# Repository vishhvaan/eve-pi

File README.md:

The EVE is an open framework for an automated continuous culture system.

  - Easy to use for programmers and non-programmers
  - Cheap
  - Replicate functionality of a morbidostat/chemostat/turbidostat
  - Versatile & easily modifiable for different purposes

This device is meant to be used for the study of population dynamics and evolution.

# Build it!
Head over to [Start Building] folder to find the 3D stls and circuit schematics (along with KiCAD project). 

# Installation

1. Download and flash the [Raspbian] Buster OS on an SD card.
2. Insert the SD Card into the Pi and connect the Pi to a display, keyboard, local area network, and power.
3. Note the IP address of the device with the command:
```sh
$ ifconfig
```
4. Enter super user mode with the command:
```sh
$ sudo su
```  
5. Run the setup script by entering the command: 
```sh
$ bash <(curl -s https://raw.githubusercontent.com/vishhvaan/eve-pi/master/st_eve.sh)
```
6. Follow the on-screen instructions to install the software.
7. Navigate to the folder `scripts/live/` and copy the `sample-conf.in` to `eve-conf.ini`.
8. Edit the `eve-conf.ini` file based on the "Configuration File Parameter Definitions" file in the "Start Building" folder.\*
9. If the Pi has a browser, navigate to the web interface by accessing: http://localhost.
10. On a browser on the network, navigate to the web interface by accessing the IP address or hostname of the device (e.g. http://eve.local_domain.net).

\* If the PCB is used or the breadboard was wired like the schematic, the default values for the hardware address in the sample-conf.ini file will work.

For a headless install:

1. Download and flash the [Raspbian] Buster OS on an SD card.
2. Add a file titled `ssh` to the boot partition.
3. Insert the SD Card into the Pi and connect the Pi to the local area network and power.
4. In a seperate computer's terminal run a command to connect to the pi.
```sh
$ ssh pi@raspberrypi
```  
5. Login to the pi with the password `raspberry`
6. Continue from step 3 in the non-headless install.

## Install for Docker for ARM Devices
 
Pre-built images coming soon to Docker Hub!

### Build the Docker Image

Use the Dockerfiles in the repo to build images yourself. Use the images to spin up containers in the Pi with EVE WebUI and all the programs built-in.

#### On ARM Devices

1. [Install Docker] on the Raspberry Pi.
2. Install git on the Raspberry Pi.
```sh
$ sudo apt install -y git
```  
2. Clone the repository to the home directory.
```sh
$ sudo git clone https://github.com/vishhvaan/eve-pi.git /eve
```  
3. Move to the correct directory.
```sh
$ cd /eve
``` 
4. Run the Docker build command.
```sh
$ docker build -t eve:pi .
```  
5. Create a container.
```sh
$ docker create --name = eve1 \
    -p 80:80 \
    -p 8050:8050 \
    -e PUID=1000 \
    -e PGID=1000 \
    -v /eve/data:/data \
    eve:pi
```  
6. Start the container.
```sh
$ docker start eve1
```  

#### On UNIX-based x86/x64 Devices
Emulate the ARM environment with QEMU. Build images with the Dockerfile.arm32v7.

### Shout Outs
The EVE uses a number of open source projects to work properly:

  - [script-server] -  Script server to run programs on the Pi
  - [slack-api] - Uses the Slack API for Python for experiment monitoring
  - [plotly] - Uses Dash for real-time plotting
  - [KiCAD] - For Circuit Schematics and PCB Designs
  - [Docker] - For creating self-contained application platforms

## New Features
 
  - Configurable save locations (USB or Network)
  - Combined graphs of culture units

<!---->

License
----

MIT

   [script-server]: <https://github.com/bugy/script-server>
   [slack-api]: <https://github.com/slackapi/python-slackclient>
   [Start Building]: <https://github.com/vishhvaan/eve-pi/tree/master/Start%20Building>
   [plotly]: <https://plot.ly/dash/>
   [KiCad]: <http://www.kicad.org/>
   [Install Docker]: <https://github.com/docker/docker-install>
   [Raspbian]: <https://www.raspberrypi.org/downloads/raspbian/>
   [Docker]: <https://github.com/docker/docker-ce>

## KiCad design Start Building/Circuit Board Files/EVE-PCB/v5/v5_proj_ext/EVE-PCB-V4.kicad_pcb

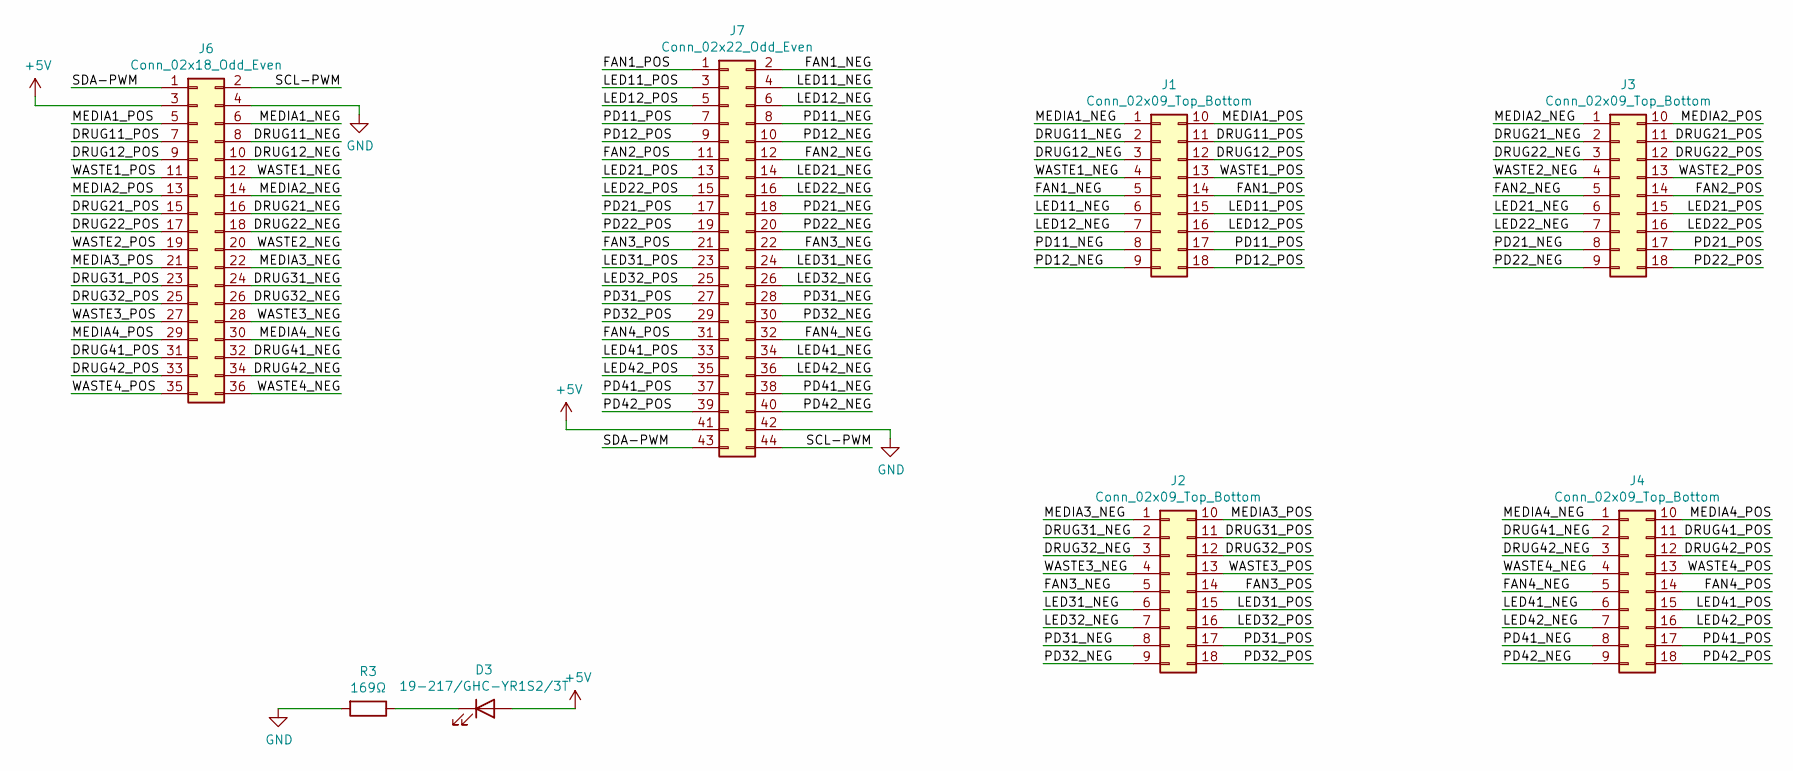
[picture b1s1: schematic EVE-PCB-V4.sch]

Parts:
D3: 19-217/GHC-YR1S2/3T; LED_0603_1608Metric; LCSC C72043
J1, J2, J3, J4: Conn_02x09_Top_Bottom; 282888-7
J6: Conn_02x18_Odd_Even; PinHeader_2x18_P2.54mm_Vertical
J7: Conn_02x22_Odd_Even; PinHeader_2x22_P2.54mm_Vertical
R3: 169Ω; R_0805_2012Metric; LCSC C17489

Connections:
+5V: D3.2 (A), J6.3, J7.41
/DRUG11_NEG: J1.2, J6.8
/DRUG11_POS: J1.11, J6.7
/DRUG12_NEG: J1.3, J6.10
/DRUG12_POS: J1.12, J6.9
/DRUG21_NEG: J3.2, J6.16
/DRUG21_POS: J3.11, J6.15
/DRUG22_NEG: J3.3, J6.18
/DRUG22_POS: J3.12, J6.17
/DRUG31_NEG: J2.2, J6.24
/DRUG31_POS: J2.11, J6.23
/DRUG32_NEG: J2.3, J6.26
/DRUG32_POS: J2.12, J6.25
/DRUG41_NEG: J4.2, J6.32
/DRUG41_POS: J4.11, J6.31
/DRUG42_NEG: J4.3, J6.34
/DRUG42_POS: J4.12, J6.33
/FAN1_NEG: J1.5, J7.2
/FAN1_POS: J1.14, J7.1
/FAN2_NEG: J3.5, J7.12
/FAN2_POS: J3.14, J7.11
/FAN3_NEG: J2.5, J7.22
/FAN3_POS: J2.14, J7.21
/FAN4_NEG: J4.5, J7.32
/FAN4_POS: J4.14, J7.31
/LED11_NEG: J1.6, J7.4
/LED11_POS: J1.15, J7.3
/LED12_NEG: J1.7, J7.6
/LED12_POS: J1.16, J7.5
/LED21_NEG: J3.6, J7.14
/LED21_POS: J3.15, J7.13
/LED22_NEG: J3.7, J7.16
/LED22_POS: J3.16, J7.15
/LED31_NEG: J2.6, J7.24
/LED31_POS: J2.15, J7.23
/LED32_NEG: J2.7, J7.26
/LED32_POS: J2.16, J7.25
/LED41_NEG: J4.6, J7.34
/LED41_POS: J4.15, J7.33
/LED42_NEG: J4.7, J7.36
/LED42_POS: J4.16, J7.35
/MEDIA1_NEG: J1.1, J6.6
/MEDIA1_POS: J1.10, J6.5
/MEDIA2_NEG: J3.1, J6.14
/MEDIA2_POS: J3.10, J6.13
/MEDIA3_NEG: J2.1, J6.22
/MEDIA3_POS: J2.10, J6.21
/MEDIA4_NEG: J4.1, J6.30
/MEDIA4_POS: J4.10, J6.29
/PD11_NEG: J1.8, J7.8
/PD11_POS: J1.17, J7.7
/PD12_NEG: J1.9, J7.10
/PD12_POS: J1.18, J7.9
/PD21_NEG: J3.8, J7.18
/PD21_POS: J3.17, J7.17
/PD22_NEG: J3.9, J7.20
/PD22_POS: J3.18, J7.19
/PD31_NEG: J2.8, J7.28
/PD31_POS: J2.17, J7.27
/PD32_NEG: J2.9, J7.30
/PD32_POS: J2.18, J7.29
/PD41_NEG: J4.8, J7.38
/PD41_POS: J4.17, J7.37
/PD42_NEG: J4.9, J7.40
/PD42_POS: J4.18, J7.39
/SCL-PWM: J6.2, J7.44
/SDA-PWM: J6.1, J7.43
/WASTE1_NEG: J1.4, J6.12
/WASTE1_POS: J1.13, J6.11
/WASTE2_NEG: J3.4, J6.20
/WASTE2_POS: J3.13, J6.19
/WASTE3_NEG: J2.4, J6.28
/WASTE3_POS: J2.13, J6.27
/WASTE4_NEG: J4.4, J6.36
/WASTE4_POS: J4.13, J6.35
GND: J6.4, J7.42, R3.2
unnamed: D3.1 (K), R3.1

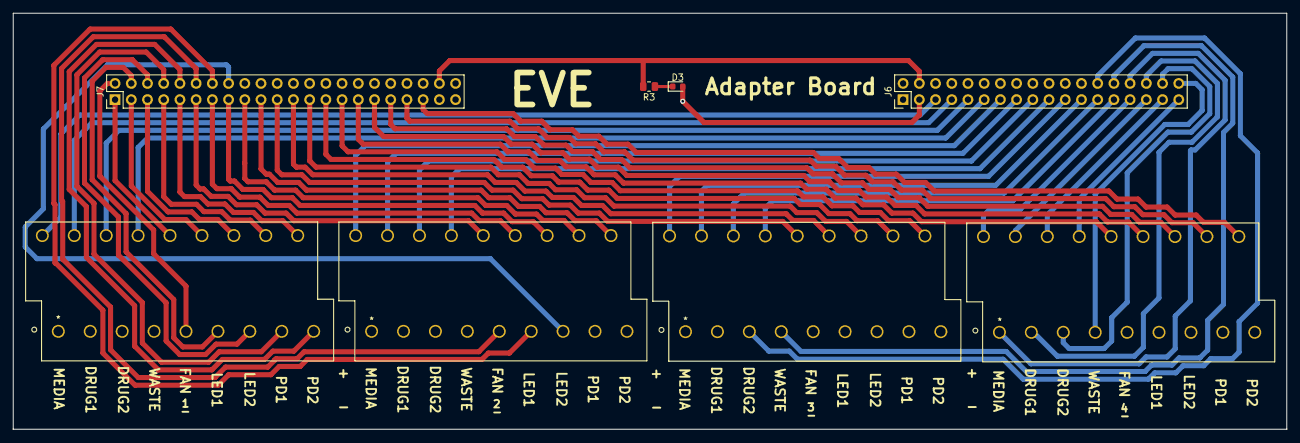
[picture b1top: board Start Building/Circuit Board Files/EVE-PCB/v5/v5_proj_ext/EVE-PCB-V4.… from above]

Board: 4 copper layers, 199.5 x 65.2 mm, 8 parts (0 on the bottom side), 77 nets.

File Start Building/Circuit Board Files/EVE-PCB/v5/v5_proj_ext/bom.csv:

Comment,Designator,Footprint,LCSC
"19-217/GHC-YR1S2/3T","D3","LED_SMD:LED_0603_1608Metric","C72043"
"Conn_02x09_Top_Bottom","J1,J2,J3,J4","ul_2828887:282888-7",""
"Conn_02x18_Odd_Even","J6","Connector_PinHeader_2.54mm:PinHeader_2x18_P2.54mm_Vertical",""
"Conn_02x22_Odd_Even","J7","Connector_PinHeader_2.54mm:PinHeader_2x22_P2.54mm_Vertical",""
"169Ω","R3","Resistor_SMD:R_0805_2012Metric","C17489"

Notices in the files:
parts and their libraries:
Copyright 2016 Accelerated Designs. All rights reserved.
